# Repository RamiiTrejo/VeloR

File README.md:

[README.md](https://github.com/user-attachments/files/22640474/README.md)
# Velocista "VeloR" - Robot Seguidor de Línea

## Descripción

El velocista "VeloR" es un robot seguidor de línea diseñado para competir en desafíos de velocidad y precisión. Este repositorio posee el diseño de hardware, firmware, 3D relacionados con VeloR. Aquí encontrarás toda la información necesaria para comprender el robot seguidor de línea VeloR.

## Características principales

- **Seguimiento de línea**: VeloR utilizará la regleta QTR8A para seguir líneas con precisión y rapidez.

- **Velocidad**: Utiliza unos motores de 3600RPM para alcanzar altas velocidades y realizar maniobras bruscas en conjunto a sus ruedas que le ayudan a tener mejor agarre en la pista.

## Contenidos
- **Firmware**: En esta carpeta encontrarás el código fuente del firmware utilizado en VeloR. El firmware está escrito en lenguaje C++ y se basa en la plataforma de desarrollo ESP32. Incluye los algoritmos de control, la lógica de seguimiento de línea y la comunicación con los sensores y actuadores del robot.
- **Hardware**: Aquí se encuentran los diseños y esquemas del hardware electrónico utilizado en VeloR. Estos archivos incluyen los esquemas de conexión y los diagramas de circuitos.

## 🎉Objetivo

 El objetivo propuesto de este robot seguidor de línea **VeloR** es ir a competir en las ligas de "Carreras" en la Liga Nacional de Robotica
 
## ⚒ Componentes principales
- Microcontolador ESP32 embebido
- 2-Controlador de motores TA6586
- Batería 3S 450mAh
- DISPLAY OLED 64X128
- Motorreductor ProFast 12v 3600RPM
- RUEDAS DE SILICONA MICRO JS2114 
- Regleta de QTR8A 

## IMAGENES PCB
<div align="center">

 <br>
 <strong>FRONT VIEW</strong>
</div> 

<div align="center">

 <br>
 <strong>BACK VIEW</strong>
</div> 

<div align="center">

 <br>
 <strong>3D PCB</strong>
</div> 

<div align="center">

</div>

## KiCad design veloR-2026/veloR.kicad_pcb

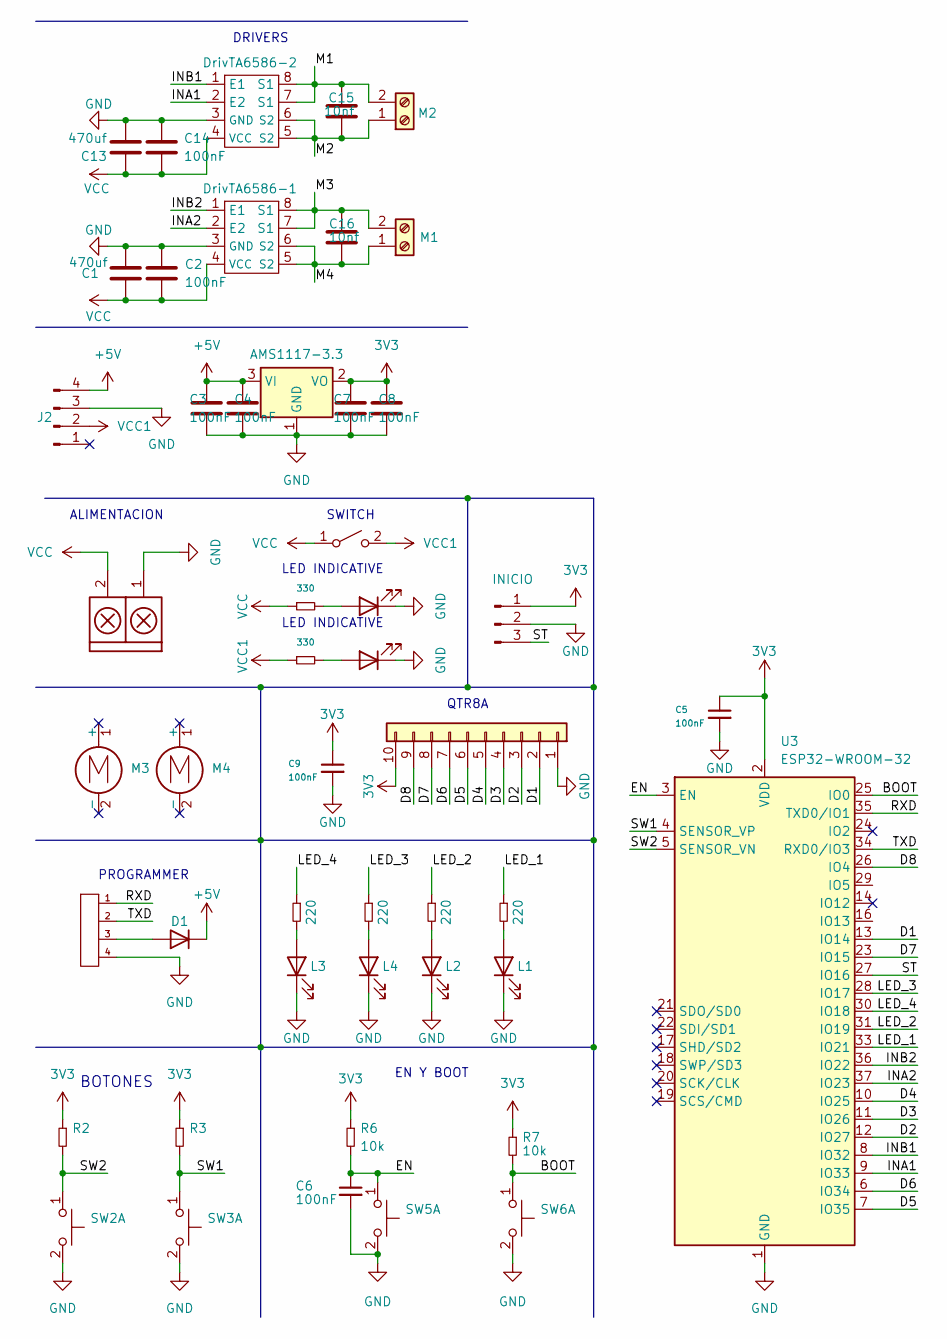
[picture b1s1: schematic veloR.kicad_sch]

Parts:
Alimentacion1: TB_1X2; AMASS_XT30U-M_1x02_P5.0mm_Vertical
C1, C13: 470uf; CP_EIA-7343-30_AVX-N_HandSolder
C2, C3, C4, C5, C6, C7, C8, C9, C14: 100nF; C_0805_2012Metric_Pad1.18x1.45mm_HandSolder
C15, C16: 10nf; C_0805_2012Metric_Pad1.18x1.45mm_HandSolder
D1: D; D_SMA
D2, D3: LED; LED_0805_2012Metric_Pad1.15x1.40mm_HandSolder
DrivTA6586-1, DrivTA6586-2: DIP-8_W7.62mm
J2: Conn_01x04_Pin; Step_Down_Mini
J3: INICIO; PinHeader_1x03_P2.54mm_Vertical
J4: Conn_01x10; JST_XH_S10B-XH-A_1x10_P2.50mm_Horizontal
J9: Programador; PinHeader_1x04_P2.54mm_Horizontal
L1, L2, L3, L4: LED; LED_0805_2012Metric_Pad1.15x1.40mm_HandSolder
M1: M1; JST_XH_B2B-XH-A_1x02_P2.50mm_Vertical
M2: M2; JST_XH_B2B-XH-A_1x02_P2.50mm_Vertical
M3, M4: Motor_DC; motor pololu
R2, R3, R6, R7: 10k; R_0805_2012Metric_Pad1.20x1.40mm_HandSolder
R13, R14, R15, R16: 220; R_0805_2012Metric_Pad1.20x1.40mm_HandSolder
R17, R18: 330; R_0805_2012Metric_Pad1.20x1.40mm_HandSolder
SW1: SW_DPST_x2; PinHeader_1x03_P2.54mm_Vertical
SW2, SW3, SW5, SW6: SW_Push_Dual_x2; SW SMD 3.5X6X5
U1: AMS1117-3.3; SOT-223-3_TabPin2
U3: ESP32-WROOM-32

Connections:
3V3: C5.1, C7.1, C8.1, C9.1, J3.1, J4.10, R2.1, R3.1, R6.1, R7.1, U1.2 (VO), U3.2 (VDD)
+5V: C3.1, C4.1, D1.1 (K), J2.4, U1.3 (VI)
/BOOT: R7.2, SW6.1 (C), U3.25 (IO0)
/D1: J4.2, U3.13 (IO14)
/D2: J4.3, U3.12 (IO27)
/D3: J4.4, U3.11 (IO26)
/D4: J4.5, U3.10 (IO25)
/D5: J4.6, U3.7 (IO35)
/D6: J4.7, U3.6 (IO34)
/D7: J4.8, U3.23 (IO15)
/D8: J4.9, U3.26 (IO4)
/EN: C6.1, R6.2, SW5.1 (C), U3.3 (EN)
/INA1: DrivTA6586-2.2 (E2), U3.9 (IO33)
/INA2: DrivTA6586-1.2 (E2), U3.37 (IO23)
/INB1: DrivTA6586-2.1 (E1), U3.8 (IO32)
/INB2: DrivTA6586-1.1 (E1), U3.36 (IO22)
/LED_1: R13.1, U3.33 (IO21)
/LED_2: R14.1, U3.31 (IO19)
/LED_3: R16.1, U3.28 (IO17)
/LED_4: R15.1, U3.30 (IO18)
/M1: C15.1, DrivTA6586-2.7 (S1), DrivTA6586-2.8 (S1), M2.2
/M2: C15.2, DrivTA6586-2.5 (S2), DrivTA6586-2.6 (S2), M2.1
/M3: C16.1, DrivTA6586-1.7 (S1), DrivTA6586-1.8 (S1), M1.2
/M4: C16.2, DrivTA6586-1.5 (S2), DrivTA6586-1.6 (S2), M1.1
/RXD: J9.1, U3.35 (TXD0/IO1)
/ST: J3.3, U3.27 (IO16)
/SW1: R3.2, SW3.1 (C), U3.4 (SENSOR_VP)
/SW2: R2.2, SW2.1 (C), U3.5 (SENSOR_VN)
/TXD: J9.2, U3.34 (RXD0/IO3)
GND: Alimentacion1.1, C1.2, C2.1, C3.2, C4.2, C5.2, C6.2, C7.2, C8.2, C9.2, C13.2, C14.1, D2.1 (K), D3.1 (K), DrivTA6586-1.3 (GND), DrivTA6586-2.3 (GND), J2.3, J3.2, J4.1, J9.4, L1.1 (K), L2.1 (K), L3.1 (K), L4.1 (K), SW2.2 (D), SW3.2 (D), SW5.2 (D), SW6.2 (D), U1.1 (GND), U3.1 (GND), U3.15 (GND), U3.38 (GND), U3.39 (GND)
unnamed: D1.2 (A), J9.3
unnamed: D2.2 (A), R17.2
unnamed: D3.2 (A), R18.2
unnamed: L1.2 (A), R13.2
unnamed: L2.2 (A), R14.2
unnamed: L3.2 (A), R15.2
unnamed: L4.2 (A), R16.2
VCC: Alimentacion1.2, C1.1, C2.2, C13.1, C14.2, DrivTA6586-1.4 (VCC), DrivTA6586-2.4 (VCC), R18.1, SW1.1 (A)
VCC1: J2.2, R17.1, SW1.2 (B)

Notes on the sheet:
EN Y BOOT
BOTONES
LED INDICATIVE
SWITCH
ALIMENTACION
DRIVERS
QTR8A
PROGRAMMER

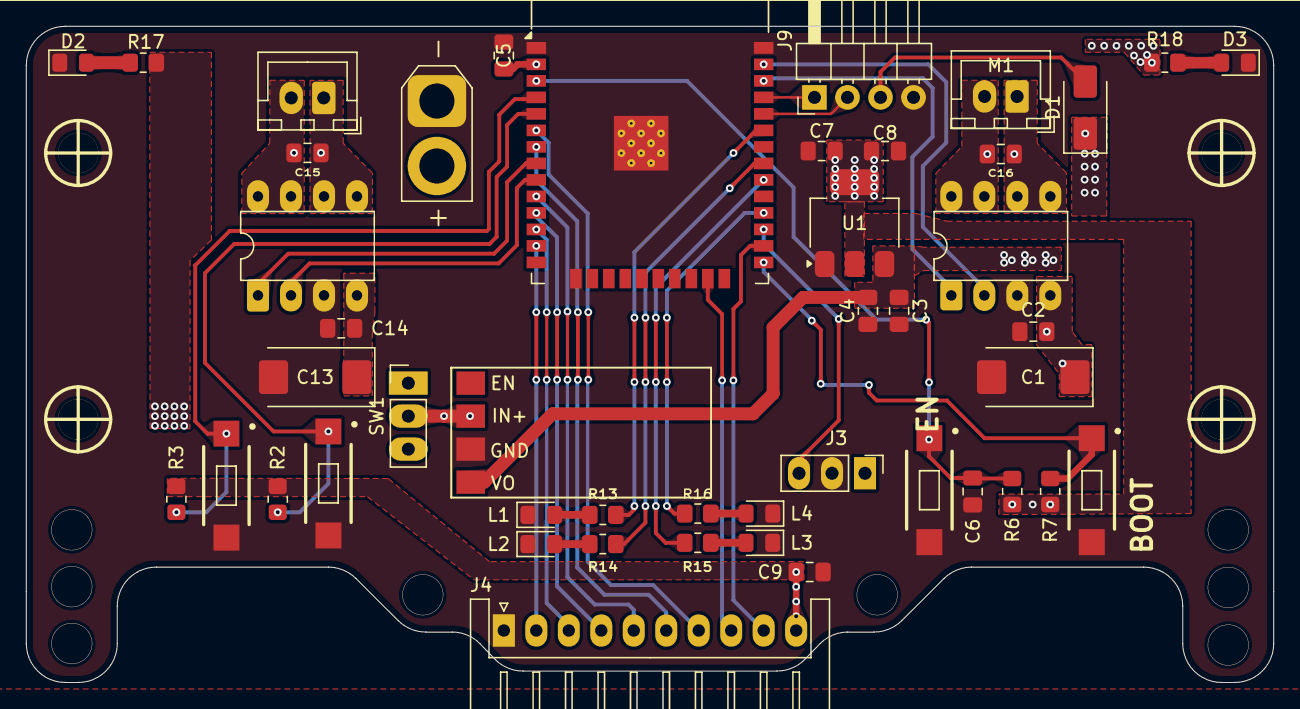
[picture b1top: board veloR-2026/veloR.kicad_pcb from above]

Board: 2 copper layers, 96.0 x 50.5 mm, 48 parts (0 on the bottom side), 39 nets.

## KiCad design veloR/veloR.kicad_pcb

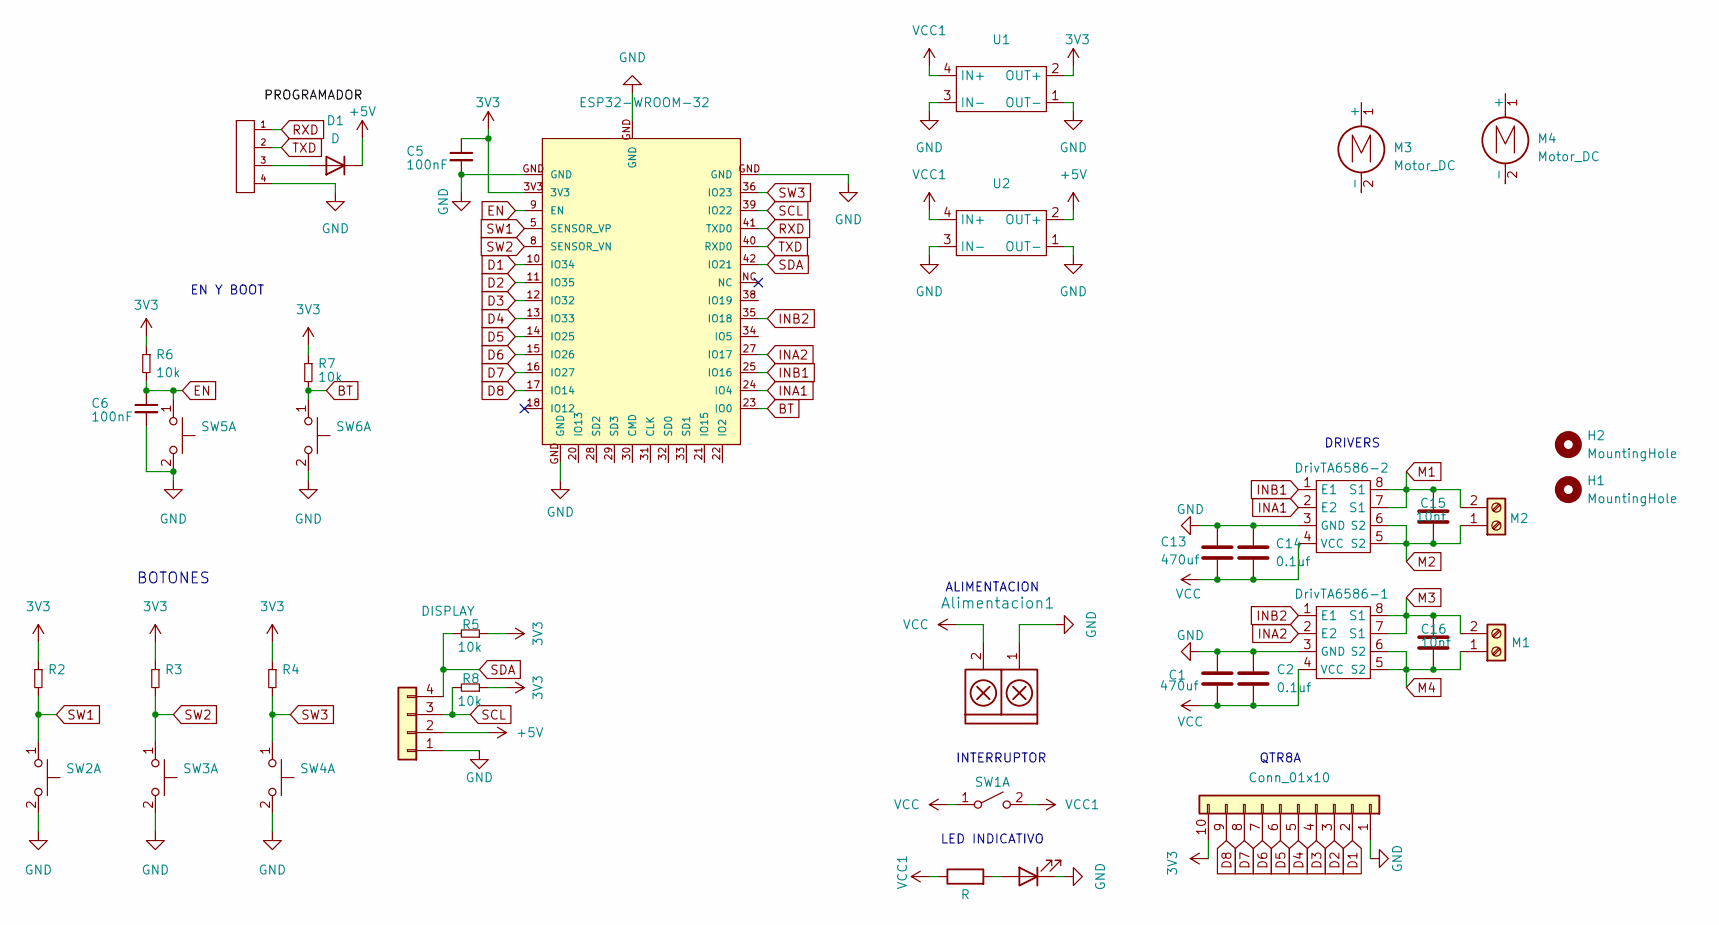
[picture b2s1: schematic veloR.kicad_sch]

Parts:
Alimentacion1: TB_1X2; AMASS_XT30U-M_1x02_P5.0mm_Vertical
C1, C13: 470uf; C_Elec_10x10.2
C2, C14: 0.1uf; C_0603_1608Metric_Pad1.08x0.95mm_HandSolder
C5, C6: 100nF; C_0805_2012Metric_Pad1.18x1.45mm_HandSolder
C15, C16: 10nf; C_0603_1608Metric_Pad1.08x0.95mm_HandSolder
D1: D; D_SMA
D2: LED; LED_1206_3216Metric_Pad1.42x1.75mm_HandSolder
DrivTA6586-1, DrivTA6586-2: DIP-8_W7.62mm
H1, H2: MountingHole; MountingHole_3.2mm_M3_DIN965
J3: DISPLAY; 128x64OLED
J4: Conn_01x10; JST_XH_S10B-XH-A-1_1x10_P2.50mm_Horizontal
J9: Programador; PinSocket_1x04_P2.54mm_Vertical
M1: M1; BORNERA2_AZUL
M2: M2; BORNERA2_AZUL
M3, M4: Motor_DC; motor 3600rpm
R1: R; R_1206_3216Metric_Pad1.30x1.75mm_HandSolder
R2, R3, R4, R5, R6, R7, R8: 10k; R_1206_3216Metric_Pad1.30x1.75mm_HandSolder
SW1: SW_DPST_x2; PinHeader_1x03_P2.54mm_Vertical
SW2, SW3, SW4, SW5, SW6: SW_Push_Dual_x2; SW 6MM 2 PIN
U1, U2: STEP DOWN MINI 360
U6: ESP32-WROOM-32; ESP32-WROOM-32E

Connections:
3V3: C5.1, J4.10, R2.1, R3.1, R4.1, R5.1, R6.1, R7.1, R8.1, U1.2 (OUT+), U6.3V3
+5V: D1.1 (K), J3.2, U2.2 (OUT+)
BT: R7.2, SW6.1 (C), U6.23 (IO0)
D1: J4.2, U6.10 (IO34)
D2: J4.3, U6.11 (IO35)
D3: J4.4, U6.12 (IO32)
D4: J4.5, U6.13 (IO33)
D5: J4.6, U6.14 (IO25)
D6: J4.7, U6.15 (IO26)
D7: J4.8, U6.16 (IO27)
D8: J4.9, U6.17 (IO14)
EN: C6.1, R6.2, SW5.1 (C), U6.9 (EN)
GND: Alimentacion1.1, C1.1, C2.1, C5.2, C6.2, C13.1, C14.1, D2.1 (K), DrivTA6586-1.3 (GND), DrivTA6586-2.3 (GND), J3.1, J4.1, J9.4, SW2.2 (D), SW3.2 (D), SW4.2 (D), SW5.2 (D), SW6.2 (D), U1.1 (OUT-), U1.3 (IN-), U2.1 (OUT-), U2.3 (IN-), U6.GND
INA1: DrivTA6586-2.2 (E2), U6.24 (IO4)
INA2: DrivTA6586-1.2 (E2), U6.27 (IO17)
INB1: DrivTA6586-2.1 (E1), U6.25 (IO16)
INB2: DrivTA6586-1.1 (E1), U6.35 (IO18)
M1: C15.1, DrivTA6586-2.7 (S1), DrivTA6586-2.8 (S1), M2.2
M2: C15.2, DrivTA6586-2.5 (S2), DrivTA6586-2.6 (S2), M2.1
M3: C16.1, DrivTA6586-1.7 (S1), DrivTA6586-1.8 (S1), M1.2
M4: C16.2, DrivTA6586-1.5 (S2), DrivTA6586-1.6 (S2), M1.1
unnamed: D1.2 (A), J9.3
unnamed: D2.2 (A), R1.2
RXD: J9.1, U6.41 (TXD0)
SCL: J3.3, R8.2, U6.39 (IO22)
SDA: J3.4, R5.2, U6.42 (IO21)
SW1: R2.2, SW2.1 (C), U6.5 (SENSOR_VP)
SW2: R3.2, SW3.1 (C), U6.8 (SENSOR_VN)
SW3: R4.2, SW4.1 (C), U6.36 (IO23)
TXD: J9.2, U6.40 (RXD0)
VCC: Alimentacion1.2, C1.2, C2.2, C13.2, C14.2, DrivTA6586-1.4 (VCC), DrivTA6586-2.4 (VCC), SW1.1 (A)
VCC1: R1.1, SW1.2 (B), U1.4 (IN+), U2.4 (IN+)

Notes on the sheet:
EN Y BOOT
BOTONES
INTERRUPTOR
ALIMENTACION
DRIVERS
QTR8A
LED INDICATIVO

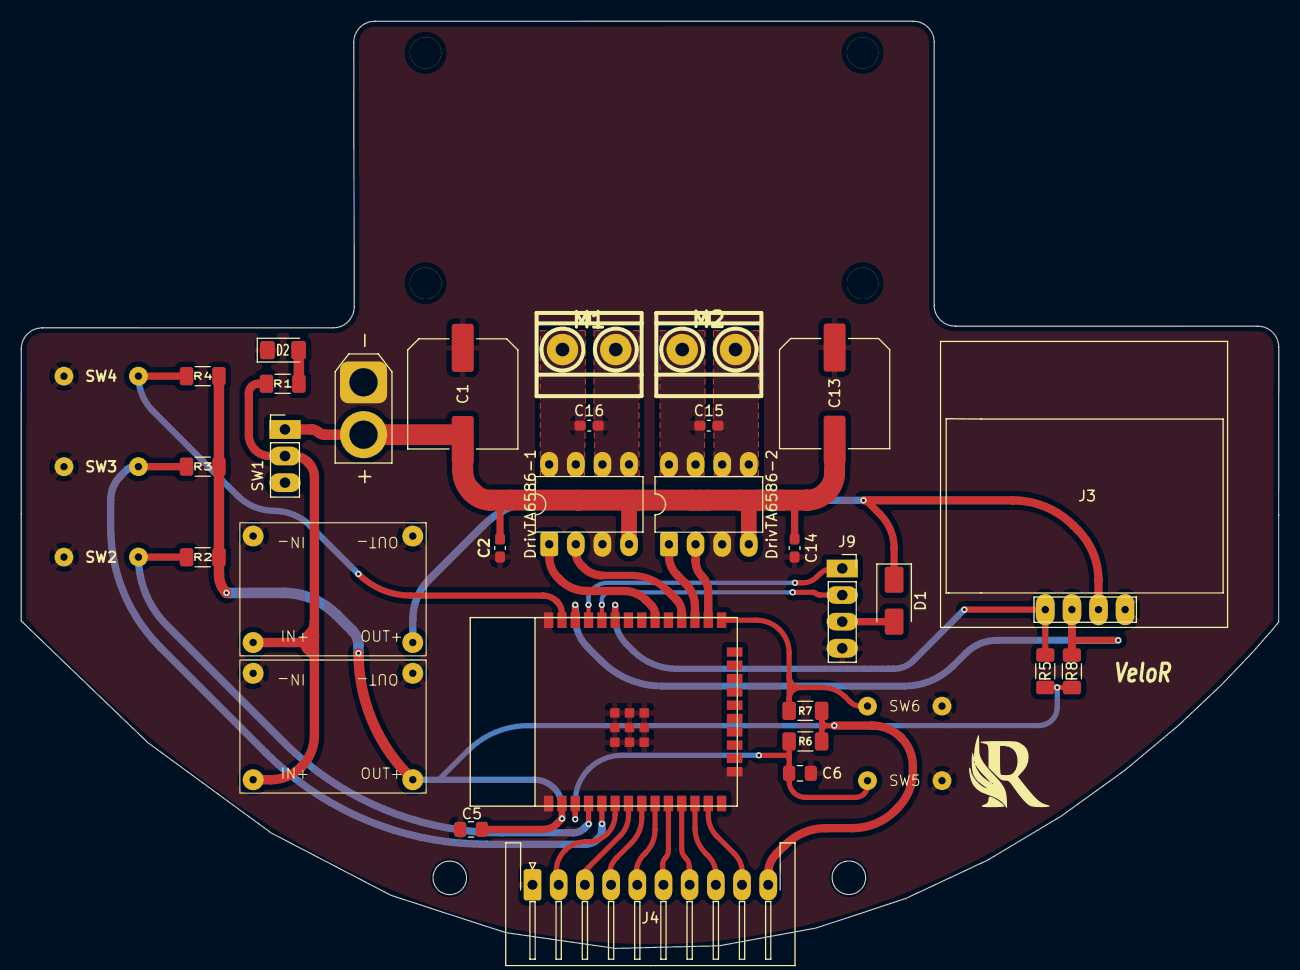
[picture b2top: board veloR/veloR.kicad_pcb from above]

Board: 2 copper layers, 120.1 x 88.5 mm, 39 parts (0 on the bottom side), 32 nets.

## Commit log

2025-10-03 Add files via upload
    MODIFIQUE PANTALLA, ACOMODE COSAS, ETC
2025-10-13 Add files via upload
    en este archivo se cambio los reguladores de tension por step down mini 360
